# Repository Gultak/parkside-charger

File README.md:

# Parkside X20V under-shelf charger, up to 16 slots (ESP32-C6 / ESPHome)

The rack screws to the underside of a shelf. Up to 16 Parkside X20V packs slide in from the front
and hang from rails, as they do on a tool. Each slot has its **own CC/CV charger IC**. An
**ESP32-C6 running ESPHome** controls all of them: it charges to a **battery-friendly level**
(92 % "ready", 60 % "storage", 100 % on demand). It reports **presence, charge state,
temperature, internal resistance, estimated capacity, self-discharge and an overall health
verdict** for every slot to Home Assistant.

| | |
|---|---|
| Slots | 1–16 printed modules, 86 mm pitch, one per battery. They **slot into each other** with a full-length sliding dovetail. 16 slots = two rows of 8 (68.8 cm each) |
| Slot board | 72 × 47.5 mm, 4 layers. LTC4162-LAD: 5S Li-ion, I²C-programmable 3.81–4.20 V/cell, 0.1–3.2 A, telemetry and battery-resistance measurement. PCA9554 for switch, LED and bleed resistor. **KiCad design + Gerbers in `electronics/slot-board/`** |
| Controller board | 112 × 64 mm, 4 layers. ESP32-C6 D1 in Dupont sockets, 2 × TCA9548A (16 I²C channels), switched 24 V to two slot chains, 5 V regulator, voltage sensing, buzzer. **KiCad design + Gerbers in `electronics/controller-board/`** |
| Wiring | 24 V **daisy-chained** slot to slot with XT30 cables (polarised and gendered: a cable can only go OUT → IN, the right way round), plus one 4-wire JST-XH I²C cable per slot to the controller. Every cable can be plugged in with the enclosures closed |
| Power | Mean Well **LOP-300-24** open-frame PSU with a PWM fan on the lid, built into the controller box in its own mains compartment. The battery-side budget (7 A, 10 A while the fan runs) is shared across the slots |
| Presence | Microswitch per slot, with the pack's BMS signal (ID contact) and voltage as a fallback |
| Safety | Per-slot fuses on both sides, the pack's BMS signal gates charging, slot NTC window 5–45 °C plus JEITA, charge timeout, fault latching, ambient limit, default-off soft-start bus switch, **70 °C thermal cut-out in the AC line** |
| Estimated cost | DigiKey order about €102 for the controller and power supply plus about €23 per slot (€229 for 10), with the remaining parts at hand; PCBs extra ([BOM.md](BOM.md)) |

## Contents

| Path | What |
|---|---|
| `mechanical/parkside_shelf_charger.scad` | Parametric OpenSCAD model: slot module (interlocking), end modules, clip-on bay cover, rail and joint test gauges, controller box |
| `mechanical/stl/` | STLs exported with the measured rail dimensions. Test-fit the gauges first |
| `docs/mechanical.md` | How to measure the pack, test prints, printing, mounting, cabling |
| `electronics/electronics.md` | Architecture, design decisions, pin maps, power budget, safety |
| `electronics/slot-board/` | KiCad 9 project, Gerbers, BOM and pick-and-place for the slot board |
| `electronics/controller-board/` | KiCad 9 project, Gerbers, BOM and pick-and-place for the controller board |
| `tools/agent-tools/` | Submodule [Gultak/agent-tools](https://github.com/Gultak/agent-tools) with the generator (`kicadgen`) that builds both boards from `tools/design.py` + `tools/layout.py` and `electronics/pcl_lib.py`. Run `git submodule update --init` after cloning |
| `HANDOFF.md` | Project state, decisions and gotchas for picking the work up in a new session |
| `procurement/` | DigiKey upload CSVs and the BOM generator (`tools/`) |
| `BOM.md` | Bill of materials with rough prices and vendor links (DigiKey Ireland, Amazon.ie) |
| `esphome/` | ESPHome config + external component (`parkside_charger`, `parkside_slot`) |
| `esphome/tests/sim/` | Host simulation of the charging logic (fake LTC4162 + battery model) |
| `docs/firmware.md` | Charging strategy, entities, LED legend, health heuristics, bring-up |

## Using the ESPHome components

`esphome/parkside-charger.yaml` loads the custom components from the local `esphome/components`
folder. To use them from GitHub instead (for example from your Home Assistant ESPHome add-on),
replace the `external_components` block with:

```yaml
external_components:
  - source:
      type: git
      url: https://github.com/Gultak/parkside-charger
      ref: main
      path: esphome/components
    components: [parkside_charger, parkside_slot]
```

## Build order

1. **Check a pack** (electronics.md §2): confirm which contact reads about 10–12 kΩ to B− (the
   BMS/ID line). Charging on B+/B− is confirmed.
2. **Measure the pack and print the gauges**, then adjust the `.scad` parameters until they fit.
   Print one module.
3. **Order the boards:** one controller board, plus a few slot boards to start.
4. **Bring up** the controller, then one slot, with a lab supply (firmware.md, checklist).
5. Test one complete slot end to end. Then build the rest.

## Open items you need to verify

- **Contact height** (`contact_z`) is still an estimate, and the front end/latch pocket are
  copied from a reference holder. Print
  `gauge.stl` and `end_gauge.stl` and test them on a pack before printing full modules.
- **Board review:** a custom router routed both PCBs automatically. They pass KiCad's DRC with no
  errors, but have a look in KiCad before ordering. Each board's README lists what to check.
- **The LTC4162-L register map and scaling** have been checked against the datasheet (Rev A)
  and the Linux driver. Still compare the voltage and current readings with a meter during
  bring-up, because sense-resistor tolerances apply.

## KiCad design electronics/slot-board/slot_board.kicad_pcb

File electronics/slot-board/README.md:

# Slot board (KiCad 9)

One per battery slot. It holds the LTC4162-LAD 5S Li-ion charger, the PCA9554 slot I/O
(presence switch, RGB LED, bleed resistor), and the I²C and 24 V connectors.
**72 × 47.5 mm, 4 layers** (In1/In2 = solid GND planes), all parts on the top side. A **10 mm
hole** at (40.5, 25) gives screwdriver access to the module's rear mounting screw.

| Top (parts side) with silkscreen | Bottom copper |
|---|---|
|  |  |
| **Inner layer 1** (In1) | **Inner layer 2** (In2) |
|  |  |

**Why 4 layers?** Two would work electrically, but the LTC4162 is a 1.5 MHz buck converter
switching several amps: a solid GND plane directly under the top layer keeps the hot loop small,
the current-sense lines quiet and the EMI low, and spreads the heat of the QFN, inductor and
MOSFETs. For small boards like this one, 4 layers cost only a little more than 2 at JLCPCB,
so it isn't worth the risk.

| File | |
|---|---|
| `slot_board.kicad_pro / .kicad_sch / .kicad_pcb` | KiCad 9 project: open with KiCad 9 or newer |
| `pcl.kicad_sym`, `sym-lib-table` | Custom symbols (LTC4162-LAD, PCA9554, Power33 MOSFET, ESD array, ...) |
| `slot_board_schematic.pdf` | Schematic |
| `fab/slot_board_gerbers.zip` | Gerbers + Excellon drill, ready to upload (e.g. JLCPCB: 4 layers, 1.6 mm, 1 oz) |
| `fab/slot_board_bom.csv`, `fab/slot_board_cpl.csv` | BOM and pick-and-place positions |
| `drc_report.txt` | KiCad DRC result |
| `tools/` | `design.py` + `layout.py`: **edit these, not the KiCad files**, then re-run `build.py` (see below) |

## Circuit

- The charger is the LTC4162-L datasheet (Rev A) typical application *"2-cell 3.2 A charger with
  PowerPath"*, set to **5 cells** (CELLS1 = CELLS0 = VCC2P5):
  - RT = 63.4 kΩ, which gives 1.5 MHz switching
  - L1 = 6.8 µH XAL6060
  - R_SNSB = R_SNSI = 10 mΩ (max 3.2 A charge / input)
  - INFET and BATFET are N-channel FDMC8327L
- **Input:** J1 (24 V IN, XT30PW-M male) and J6 (24 V OUT, XT30PW-F female) are right-angle XT30s
  sticking out of the rear edge, connected straight through so the slots **daisy-chain**. XT30s
  are polarised and gendered, so a chain cable only fits OUT → IN, the right way round. The pass-through copper is a
  pour on both outer layers (for the chain current), and GND passes through the two inner planes.
  Behind the connectors come a 5 A fuse, an SMBJ26A TVS and 47 µF of bulk capacitance.
- **Battery:** J3 (B+, B−, ID) goes through a mandatory 5 A fuse F2. The pack charges directly on
  B+/B−.
- **Pack BMS signal (ID contact):** 10 kΩ pull-up to 5 V (R15, like the Parkside charger), RC
  filter 100 kΩ / 4.7 µF (R16/C15) against the pack's short releases, TLV7031 comparator U4 at
  4.55 V (R17/R18) → PCA9554 IO6. High = released = BMS fault / deep discharge / no pack.
- **Thermistor:** the LTC4162 reads RT1, a 10 kΩ NTC (B 3380) at the front edge next to the
  battery contacts, with NTCBIAS 10 kΩ 0.1 %. The pack's own NTC is in series with its BMS
  transistor and pulsed, so it is not used.
- **I²C:** J2 (JST-XH 4: 5V, GND, SDA, SCL) has 100 Ω series resistors and a PESD5V0S2UT.
  LTC4162 @0x68 and PCA9554 @0x20 share the bus. The slot bus runs at 5 V; the TCA9548A on the
  controller shifts the level.
- **PCA9554:**
  - IO0: presence switch (J4)
  - IO1–3: common-cathode RGB LED (J5), with 560/270/270 Ω
  - IO4: bleed MOSFET Q3, which switches 2 × 100 Ω / 2 W (about 0.1 A) across the battery
  - IO5: SMBALERT

## Layout

The layout follows the LTC4162 datasheet's *PCB Layout Considerations*:
- The VOUT bypass capacitors C3/C4 sit directly at pins 27/28 → 23/24. SW (pins 25/26) leaves
  between their pads straight into L1, which keeps the hot loop minimal.
- **Kelvin traces:** CLP/CLN go to the RSNSI pads, and CSP/CSN/BATSENS+ go to the RSNSB pads.
- The INTVCC, VCC2P5 and VOUTA capacitors sit next to their pins. Every GND pad has its own via
  to the planes, and the exposed pad has 9 thermal vias.
- The input parts (TVS, bulk capacitor, fuse) sit in the left column next to the input FET, so
  the 24 V terminals and the I²C connector are as far forward as possible.
- The pack-ID circuit (R15–R18, C15, C16, comparator U4) sits in the front-left corner next to
  J3's ID terminal, so the ID line from the pack is short; only the comparator's logic output
  crosses the board to the PCA9554.
- The bleed resistors lie flat in the right half, away from the IC. Mount them 2–3 mm above the
  board.
- The **screwdriver hole** (board cutout, copper kept 0.5 mm away on all layers) sits between the
  charger and the PCA9554. It must stay aligned with `pcb_hole` in the 3D model.
- The board's long edges ride in the card guides of the printed bay, so parts keep 2 mm away
  from them.

**DRC:** no errors or unconnected items. What remains are 5 silkscreen cosmetics, which the fab
house clips at the pads, and `lib_footprint_issues` warnings. Those appear only because the
generator runs without the global library table; KiCad's GUI doesn't show them.

## Regenerating

```bash
cd tools
/usr/bin/python3 build.py          # schematic + netlist check, PCB (route, fill, DRC), fab files, renders
/usr/bin/python3 build.py sch      # only the schematic + netlist check
```

`design.py` is the single source of truth for parts and nets. `layout.py` holds the placement,
pour shapes, routing priorities, silkscreen and schematic sheet positions. The generator itself
(`kicadgen`) is shared with the controller board and lives in the `tools/agent-tools` submodule
([Gultak/agent-tools](https://github.com/Gultak/agent-tools)); the boards' custom symbols and
footprints are in `../pcl_lib.py`. It needs KiCad 9 (`kicad-cli` and the
`pcbnew` Python module) with the standard KiCad 9 footprint and symbol libraries, so the
footprints in the board match the libraries KiCad 9 checks them against.

## Before ordering: check these

1. **FDMC8327L footprint:** it uses KiCad's `VSON-8_3.3x3.3mm_P0.65mm_NexFET` (the same
   S-S-S-G / drain-pad pinout as Power33). Compare it with the Onsemi land pattern, or pick a
   MOSFET specified for that footprint.
2. **Connector orientation:** check in the 3D viewer that J3's wire entry faces the front edge
   (towards the contact block) and that the XT30 noses of J1/J6 stick out of the rear edge.
3. **Review the routing in KiCad:** a custom grid router routed this board automatically.
   Electrically it is DRC-clean, but a human pass is recommended, especially:
   - the comparator output (U4 → PCA9554 IO6) across the board
   - the I²C pair along the middle of the board
4. **First bring-up:** use a current-limited lab supply. See `docs/firmware.md`, *Bring-up checklist*.

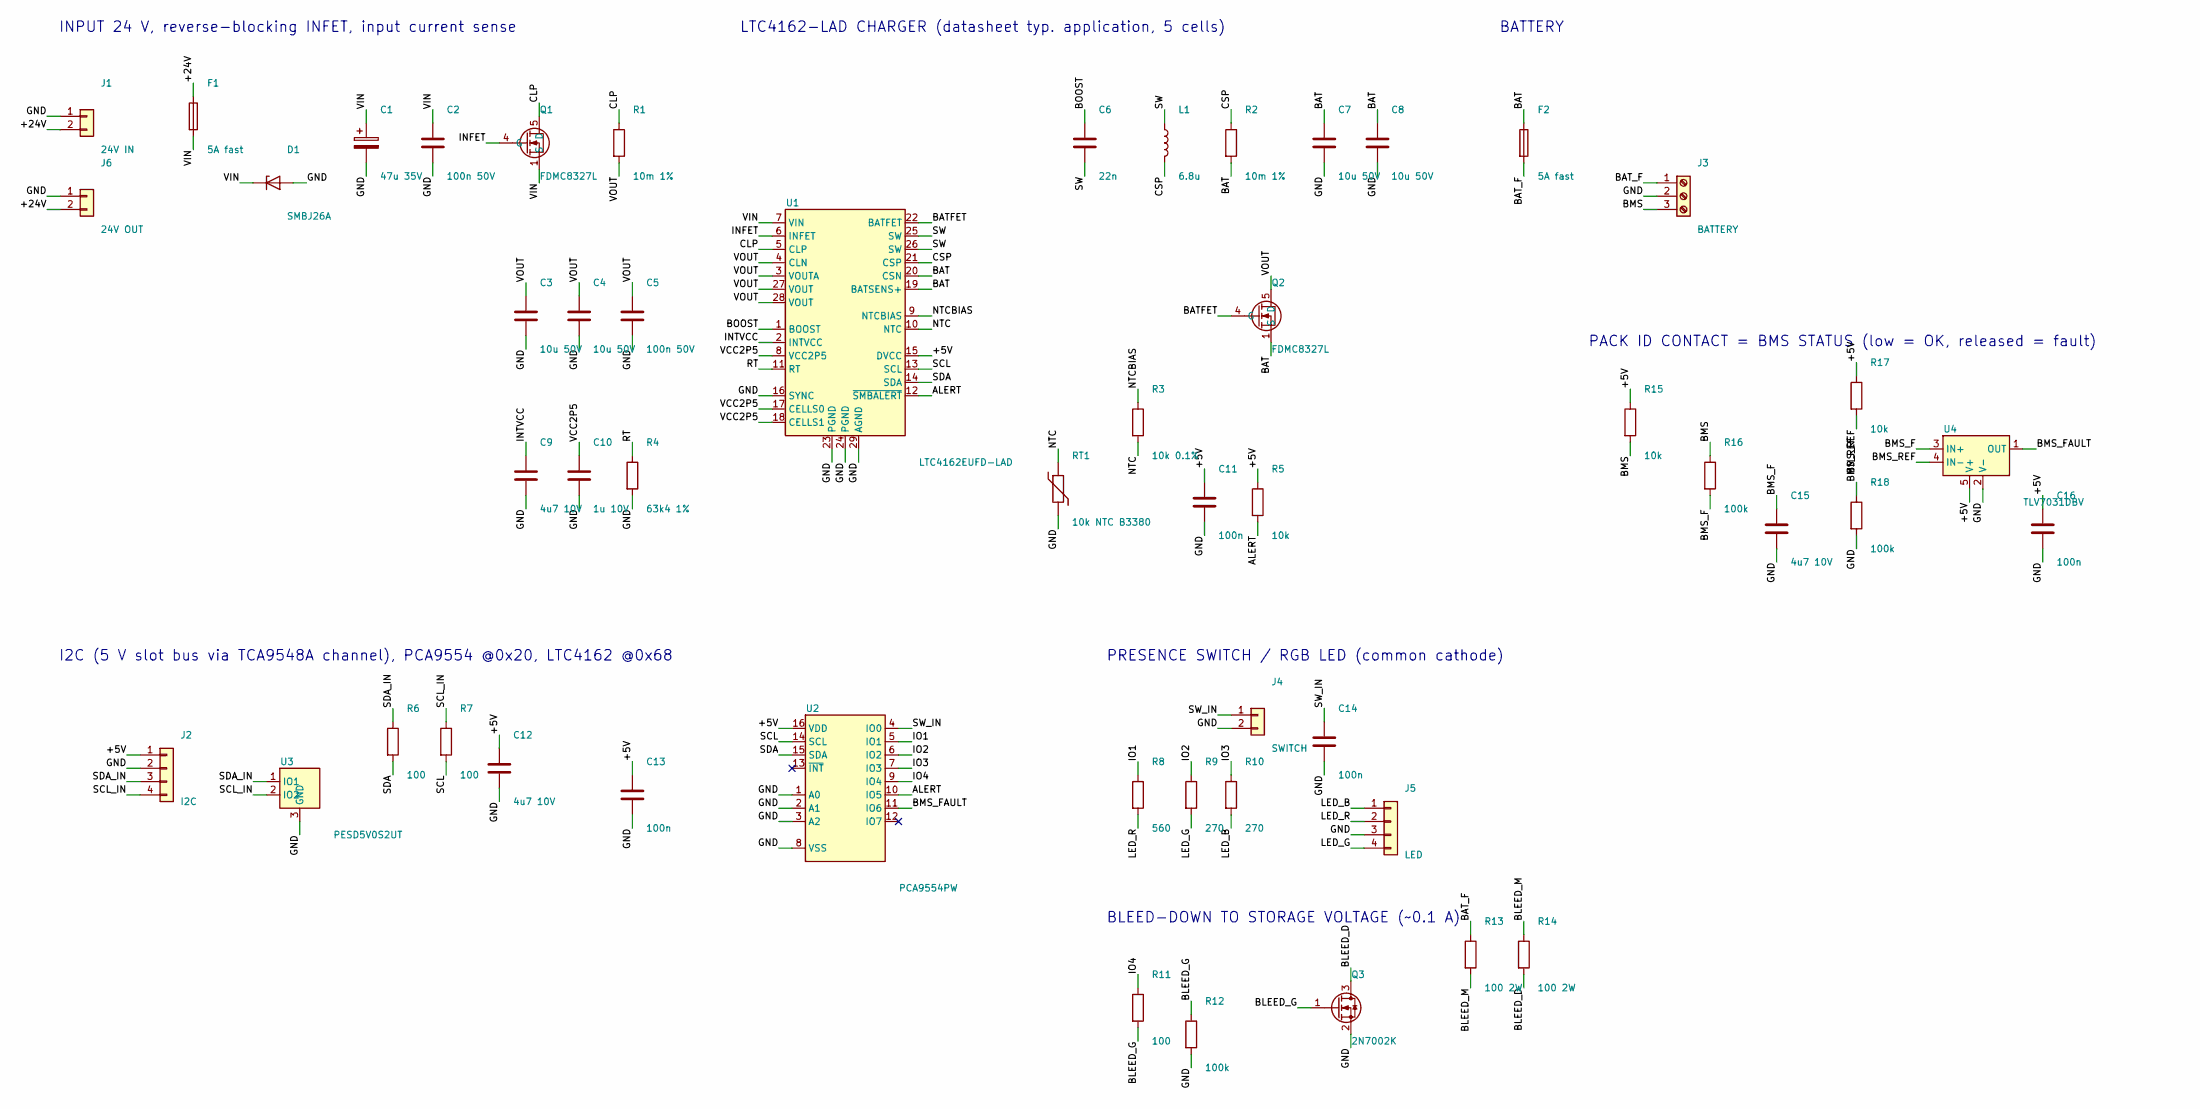
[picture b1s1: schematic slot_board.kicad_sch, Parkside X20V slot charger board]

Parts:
C1: 47u 35V; CP_Elec_6.3x7.7; MPN Aluminium-polymer/electrolytic, low-Q d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
C2: 100n 50V; C_0603_1608Metric; MPN X7R
C3: 10u 50V; C_1206_3216Metric; MPN X7R, hot-loop cap: directly at pins 27/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
C4: 10u 50V; C_1206_3216Metric; MPN X7R
C5: 100n 50V; C_0603_1608Metric; MPN X7R, VOUTA bypass
C6: 22n; C_0603_1608Metric; MPN X7R >= 6.3 V, BOOST cap
C7: 10u 50V; C_1206_3216Metric; MPN X7R, BATSENS+ bypass
C8: 10u 50V; C_1206_3216Metric; MPN X7R, battery-side bulk
C9: 4u7 10V; C_0603_1608Metric; MPN X7R
C10: 1u 10V; C_0603_1608Metric; MPN X7R
C11: 100n; C_0603_1608Metric; MPN DVCC bypass
C12: 4u7 10V; C_0603_1608Metric; MPN 5 V bulk
C13: 100n; C_0603_1608Metric
C14: 100n; C_0603_1608Metric; MPN debounce
C15: 4u7 10V; C_0603_1608Metric; MPN X5R
C16: 100n; C_0603_1608Metric; MPN U4 bypass
D1: SMBJ26A; D_SMB; MPN TVS 26 V unidirectional (K = pin 1)
F1: 5A fast; Fuse_1206_3216Metric; MPN Littelfuse 0466005.NR (1206, 5 A, very 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
F2: 5A fast; Fuse_1206_3216Metric; MPN Littelfuse 0466005.NR - mandatory, batt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
J1: 24V IN; AMASS_XT30PW-M_1x02_P2.50mm_Horizontal; MPN Amass XT30PW-M (male, right angle): 24 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
J2: I2C; JST_XH_B4B-XH-A_1x04_P2.50mm_Vertical; MPN JST B4B-XH-A: 5V, GND, SDA, SCL
J3: BATTERY; TerminalBlock_Phoenix_MKDS-1,5-3_1x03_P5.00mm_Horizontal; MPN 5.0 mm 3-pole screw terminal (e.g. Phoe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
J4: SWITCH; PinHeader_1x02_P2.54mm_Vertical; MPN 2.54 mm pin header (Dupont cable): pres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
J5: LED; PinHeader_1x04_P2.54mm_Vertical; MPN 2.54 mm pin header in the LED's lead or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
J6: 24V OUT; AMASS_XT30PW-F_1x02_P2.50mm_Horizontal; MPN Amass XT30PW-F (female, right angle): 2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
L1: 6.8u; L_Vishay_IHLP-2525; MPN Vishay IHLP2525CZER6R8M01 (6.8 uH, IHLP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
Q1: FDMC8327L; VSON-8_3.3x3.3mm_P0.65mm_NexFET; MPN INFET, 40 V logic-level N-MOSFET (Power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
Q2: FDMC8327L; VSON-8_3.3x3.3mm_P0.65mm_NexFET; MPN BATFET, 40 V logic-level N-MOSFET (only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
Q3: 2N7002K; SOT-23; MPN 60 V, 0.3 A
R1: 10m 1%; R_2512_6332Metric; MPN RSNSI, 1 W current sense
R2: 10m 1%; R_2512_6332Metric; MPN RSNSB, 1 W current sense
R3: 10k 0.1%; R_0603_1608Metric; MPN NTC bias, low TC (25 ppm)
R4: 63k4 1%; R_0603_1608Metric; MPN 1.5 MHz
R5: 10k; R_0603_1608Metric; MPN SMBALERT pull-up
R6, R7, R11: 100; R_0603_1608Metric
R8: 560; R_0603_1608Metric; MPN red
R9: 270; R_0603_1608Metric; MPN green
R10: 270; R_0603_1608Metric; MPN blue
R12, R16: 100k; R_0603_1608Metric
R13, R14: 100 2W; R_Axial_DIN0414_L11.9mm_D4.5mm_P15.24mm_Horizontal; MPN metal oxide 2 W, mount 2-3 mm above the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
R15: 10k; R_0603_1608Metric; MPN ID pull-up
R17: 10k; R_0603_1608Metric
R18: 100k; R_0603_1608Metric; MPN -> 4.55 V
RT1: 10k NTC B3380; R_0603_1608Metric; MPN Murata NCP18XH103F03RB (10k, B25/50 338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
U1: LTC4162EUFD-LAD; QFN-28-1EP_4x5mm_P0.5mm_EP2.65x3.65mm_ThermalVias; MPN Analog Devices LTC4162EUFD-LAD#PBF (I2C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
U2: PCA9554PW; TSSOP-16_4.4x5mm_P0.65mm; MPN NXP PCA9554PW (or TCA9554PWR), address 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
U3: PESD5V0S2UT; SOT-23; MPN Nexperia PESD5V0S2UT
U4: TLV7031DBV; SOT-23-5; MPN TI TLV7031DBVR (push-pull, rail-to-rail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

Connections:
/+5V: C11.1, C12.1, C13.1, C16.1, J2.1, R5.1, R15.1, R17.1, U1.15 (DVCC), U2.16 (VDD), U4.5 (V+)
/+24V: F1.1, J1.2, J6.2
/ALERT: R5.2, U1.12 (~SMBALERT), U2.10 (IO5)
/BAT: C7.1, C8.1, F2.1, Q2.1 (S), Q2.2 (S), Q2.3 (S), R2.2, U1.19 (BATSENS+), U1.20 (CSN)
/BATFET: Q2.4 (G), U1.22 (BATFET)
/BAT_F: F2.2, J3.1, R13.1
/BLEED_D: Q3.3 (D), R14.2
/BLEED_G: Q3.1 (G), R11.2, R12.1
/BLEED_M: R13.2, R14.1
/BMS: J3.3, R15.2, R16.1
/BMS_F: C15.1, R16.2, U4.3 (IN+)
/BMS_FAULT: U2.11 (IO6), U4.1 (OUT)
/BMS_REF: R17.2, R18.1, U4.4 (IN-)
/BOOST: C6.1, U1.1 (BOOST)
/CLP: Q1.5 (D), R1.1, U1.5 (CLP)
/CSP: L1.2, R2.1, U1.21 (CSP)
/GND: C1.2, C2.2, C3.2, C4.2, C5.2, C7.2, C8.2, C9.2, C10.2, C11.2, C12.2, C13.2, C14.2, C15.2, C16.2, D1.2 (A), J1.1, J2.2, J3.2, J4.2, J5.3, J6.1, Q3.2 (S), R4.2, R12.2, R18.2, RT1.2, U1.16 (SYNC), U1.23 (PGND), U1.24 (PGND), U1.29 (AGND), U2.1 (A0), U2.2 (A1), U2.3 (A2), U2.8 (VSS), U3.3 (GND), U4.2 (V-)
/INFET: Q1.4 (G), U1.6 (INFET)
/INTVCC: C9.1, U1.2 (INTVCC)
/IO1: R8.1, U2.5 (IO1)
/IO2: R9.1, U2.6 (IO2)
/IO3: R10.1, U2.7 (IO3)
/IO4: R11.1, U2.9 (IO4)
/LED_B: J5.1, R10.2
/LED_G: J5.4, R9.2
/LED_R: J5.2, R8.2
/NTC: R3.2, RT1.1, U1.10 (NTC)
/NTCBIAS: R3.1, U1.9 (NTCBIAS)
/RT: R4.1, U1.11 (RT)
/SCL: R7.2, U1.13 (SCL), U2.14 (SCL)
/SCL_IN: J2.4, R7.1, U3.2 (IO2)
/SDA: R6.2, U1.14 (SDA), U2.15 (SDA)
/SDA_IN: J2.3, R6.1, U3.1 (IO1)
/SW: C6.2, L1.1, U1.25 (SW), U1.26 (SW)
/SW_IN: C14.1, J4.1, U2.4 (IO0)
/VCC2P5: C10.1, U1.8 (VCC2P5), U1.17 (CELLS0), U1.18 (CELLS1)
/VIN: C1.1, C2.1, D1.1 (K), F1.2, Q1.1 (S), Q1.2 (S), Q1.3 (S), U1.7 (VIN)
/VOUT: C3.1, C4.1, C5.1, Q2.5 (D), R1.2, U1.3 (VOUTA), U1.4 (CLN), U1.27 (VOUT), U1.28 (VOUT)

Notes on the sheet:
INPUT 24 V, reverse-blocking INFET, input current sense
LTC4162-LAD CHARGER (datasheet typ. application, 5 cells)
BATTERY
I2C (5 V slot bus via TCA9548A channel), PCA9554 @0x20, LTC4162 @0x68
PRESENCE SWITCH / RGB LED (common cathode)
BLEED-DOWN TO STORAGE VOLTAGE (~0.1 A)
PACK ID CONTACT = BMS STATUS (low = OK, released = fault)

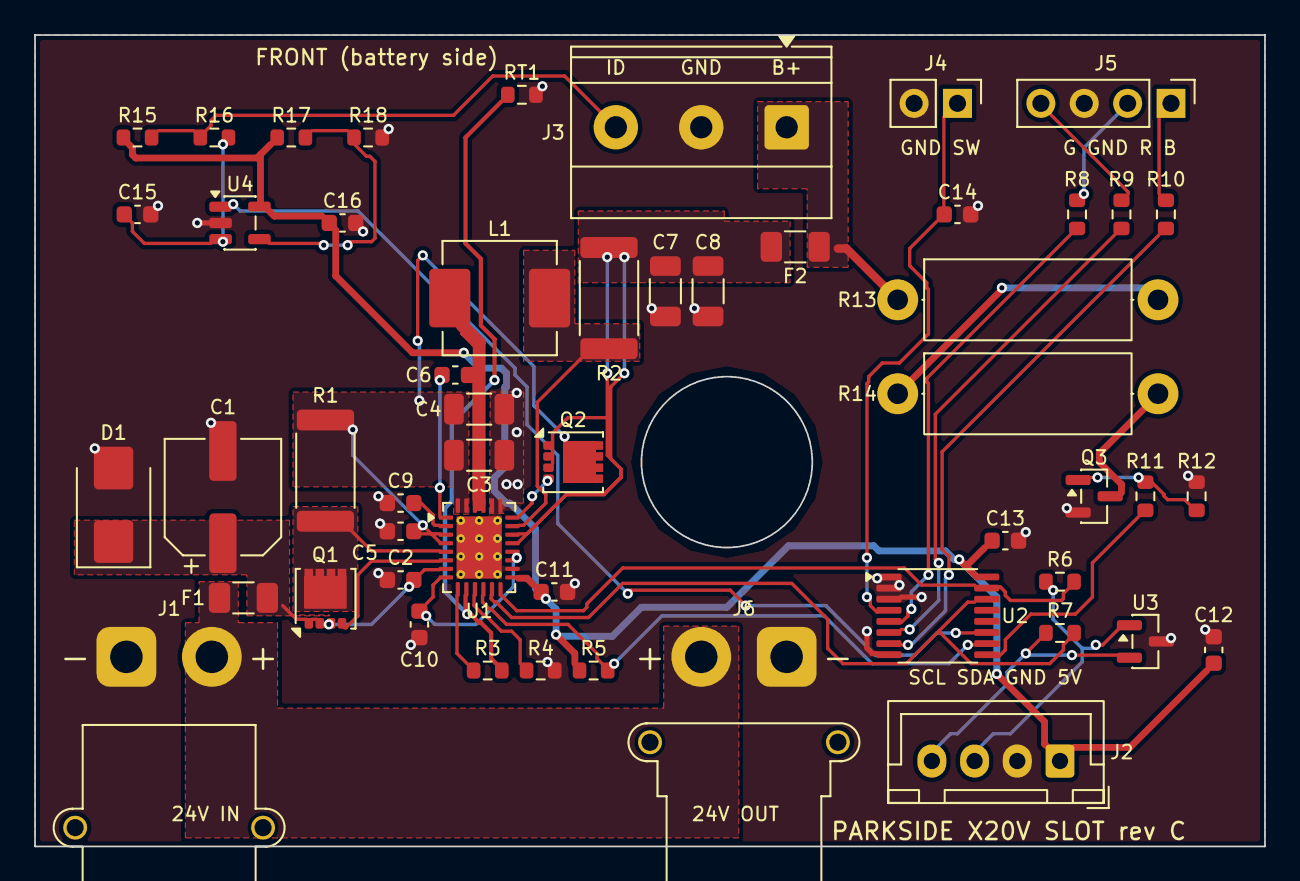
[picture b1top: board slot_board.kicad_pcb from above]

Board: 4 copper layers, 72.0 x 47.5 mm, 52 parts (0 on the bottom side), 38 nets.

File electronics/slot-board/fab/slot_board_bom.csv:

Qty,References,Value,Footprint,MPN / notes
1,C1,47u 35V,CP_Elec_6.3x7.7,"Aluminium-polymer/electrolytic, low-Q damping for hot plug"
1,C2,100n 50V,C_0603_1608Metric,X7R
1,C3,10u 50V,C_1206_3216Metric,"X7R, hot-loop cap: directly at pins 27/28 - 23/24"
1,C4,10u 50V,C_1206_3216Metric,X7R
1,C5,100n 50V,C_0603_1608Metric,"X7R, VOUTA bypass"
1,C6,22n,C_0603_1608Metric,"X7R >= 6.3 V, BOOST cap"
1,C7,10u 50V,C_1206_3216Metric,"X7R, BATSENS+ bypass"
1,C8,10u 50V,C_1206_3216Metric,"X7R, battery-side bulk"
1,C9,4u7 10V,C_0603_1608Metric,X7R
1,C10,1u 10V,C_0603_1608Metric,X7R
1,C11,100n,C_0603_1608Metric,DVCC bypass
1,C12,4u7 10V,C_0603_1608Metric,5 V bulk
1,C13,100n,C_0603_1608Metric,
1,C14,100n,C_0603_1608Metric,debounce
1,C15,4u7 10V,C_0603_1608Metric,X5R
1,C16,100n,C_0603_1608Metric,U4 bypass
1,D1,SMBJ26A,D_SMB,TVS 26 V unidirectional (K = pin 1)
1,F1,5A fast,Fuse_1206_3216Metric,"Littelfuse 0466005.NR (1206, 5 A, very fast)"
1,F2,5A fast,Fuse_1206_3216Metric,"Littelfuse 0466005.NR - mandatory, battery side"
1,J2,I2C,JST_XH_B4B-XH-A_1x04_P2.50mm_Vertical,"JST B4B-XH-A: 5V, GND, SDA, SCL"
1,L1,6.8u,L_Vishay_IHLP-2525,"Vishay IHLP2525CZER6R8M01 (6.8 uH, IHLP-2525)"
1,Q1,FDMC8327L,VSON-8_3.3x3.3mm_P0.65mm_NexFET,"INFET, 40 V logic-level N-MOSFET (Power33). Check land pattern vs. part"
1,Q2,FDMC8327L,VSON-8_3.3x3.3mm_P0.65mm_NexFET,"BATFET, 40 V logic-level N-MOSFET (only powers the IC from the battery)"
1,Q3,2N7002K,SOT-23,"60 V, 0.3 A"
1,R1,10m 1%,R_2512_6332Metric,"RSNSI, 1 W current sense"
1,R2,10m 1%,R_2512_6332Metric,"RSNSB, 1 W current sense"
1,R3,10k 0.1%,R_0603_1608Metric,"NTC bias, low TC (25 ppm)"
1,R4,63k4 1%,R_0603_1608Metric,1.5 MHz
1,R5,10k,R_0603_1608Metric,SMBALERT pull-up
3,R6 R7 R11,100,R_0603_1608Metric,
1,R8,560,R_0603_1608Metric,red
1,R9,270,R_0603_1608Metric,green
1,R10,270,R_0603_1608Metric,blue
2,R12 R16,100k,R_0603_1608Metric,
2,R13 R14,100 2W,R_Axial_DIN0414_L11.9mm_D4.5mm_P15.24mm_Horizontal,"metal oxide 2 W, mount 2-3 mm above the board"
1,R15,10k,R_0603_1608Metric,ID pull-up
1,R17,10k,R_0603_1608Metric,
1,R18,100k,R_0603_1608Metric,-> 4.55 V
1,RT1,10k NTC B3380,R_0603_1608Metric,"Murata NCP18XH103F03RB (10k, B25/50 3380, 1%)"
1,U1,LTC4162EUFD-LAD,QFN-28-1EP_4x5mm_P0.5mm_EP2.65x3.65mm_ThermalVias,Analog Devices LTC4162EUFD-LAD#PBF (I2C adjustable!)
1,U2,PCA9554PW,TSSOP-16_4.4x5mm_P0.65mm,"NXP PCA9554PW (or TCA9554PWR), address 0x20"
1,U3,PESD5V0S2UT,SOT-23,Nexperia PESD5V0S2UT
1,U4,TLV7031DBV,SOT-23-5,"TI TLV7031DBVR (push-pull, rail-to-rail input)"
